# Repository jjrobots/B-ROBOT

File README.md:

JJROBOTS B-ROBOT
=================
Self Balancing Arduino robot. Control via Smartphone/Tablet. With Fully 3D printed parts.
New: This new version include support for the new V2 board! (with integrated ESP wifi module)

All the documentation, features, how it works, build manuals and SHOP here:
URL: http://jjrobots.com/b-robot

This is the new and well improved version of the old project:
Blog: http://cienciaycacharreo.blogspot.com.es/2013/10/b-robot-un-robot-equilibrista-impreso_28.html

To install code read the install.txt instructions

JJROBOTS 2015. Science & fun!

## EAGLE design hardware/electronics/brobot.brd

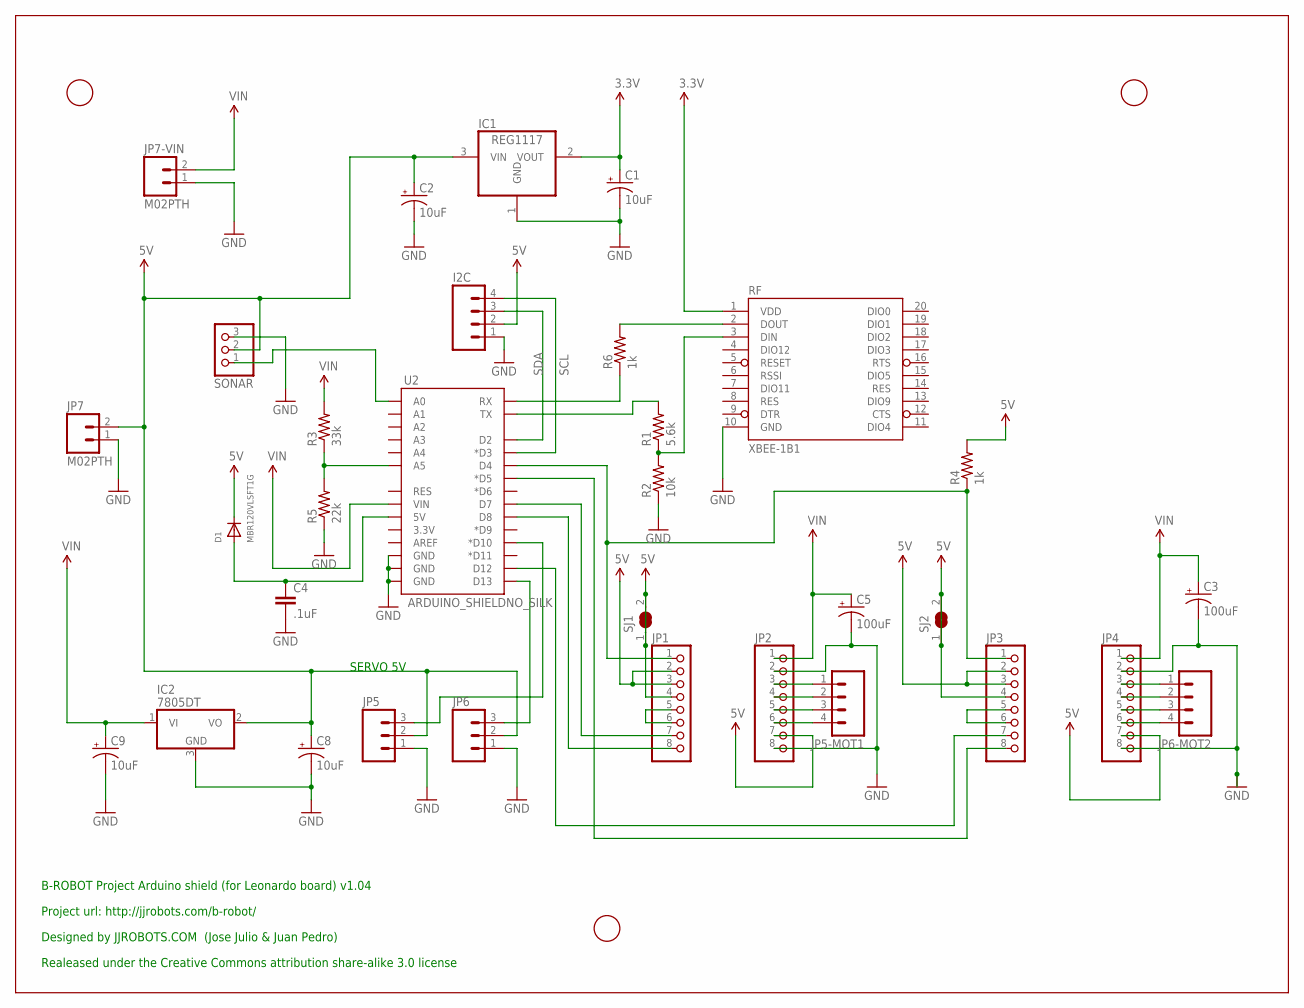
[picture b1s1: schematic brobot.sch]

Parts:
C1, C2, C8, C9: 10uF; EIA3216
C3, C5: 100uF; PANASONIC_D
C4: .1uF; 0402-CAP
D1: MBR120VLSFT1G; SOD-123
I2C: M04PTH; 1X04
IC1: REG1117; SOT223
IC2: 7805DT; TO252
JP1, JP2, JP3, JP4: PINHD-1X8; 1X08
JP5, JP6: M03PTH; 1X03
JP5-MOT1, JP6-MOT2: M04PTH; 1X04
JP7, JP7-VIN: M02PTH; 1X02
R1: 5.6k; 0805
R2: 10k; 0805
R3: 33k; 0805
R4, R6: 1k; 0805
R5: 22k; 0805
RF: XBEE-1B1; XBEE-1
SJ1, SJ2: SJW
SONAR: PINHD-1X3; 1X03
U2: ARDUINO_SHIELDNO_SILK; DUEMILANOVE_VIAS
U$1, U$2, U$3: FIDUCIAL; FIDUCIAL_1MM

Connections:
3.3V: C1.A (+), IC1.2 (VOUT), RF.1 (VDD)
5V: C2.A (+), C8.A (+), D1.C, I2C.2, IC1.3 (VIN), IC2.2 (VO), JP1.2, JP1.3, JP1.4, JP2.7, JP3.2, JP3.3, JP3.4, JP4.7, JP5.2, JP6.2, JP7.2, R4.2, SJ1.1, SJ1.2, SJ2.1, SJ2.2, SONAR.2
GND: C1.C (-), C2.C (-), C3.-, C4.2, C5.-, C8.C (-), C9.C (-), I2C.1, IC1.1 (GND), IC2.3 (GND), JP2.2, JP2.8, JP4.2, JP4.8, JP5.1, JP6.1, JP7.1, JP7-VIN.1, R2.1, R5.1, RF.10 (GND), SONAR.3, U2.GND@0 (GND), U2.GND@1 (GND), U2.GND@2 (GND)
unnamed: JP2.3, JP5-MOT1.1
unnamed: JP2.4, JP5-MOT1.2
unnamed: R6.2, RF.2 (DOUT)
unnamed: R1.1, R2.2, RF.3 (DIN)
unnamed: R1.2, U2.TX
unnamed: JP2.5, JP5-MOT1.3
unnamed: JP2.6, JP5-MOT1.4
unnamed: JP4.3, JP6-MOT2.1
unnamed: JP4.4, JP6-MOT2.2
unnamed: JP4.5, JP6-MOT2.3
unnamed: JP1.5, JP1.6
unnamed: JP3.5, JP3.6
unnamed: R3.1, R5.2, U2.A5
unnamed: R6.1, U2.RX
unnamed: SONAR.1, U2.A0
unnamed: JP4.6, JP6-MOT2.4
unnamed: JP6.3, U2.D13
unnamed: JP5.3, U2.D10 (*D10)
unnamed: JP1.8, U2.D8
unnamed: JP1.7, U2.D7
unnamed: JP1.1, JP3.1, R4.1, U2.D4
unnamed: JP3.8, U2.D5 (*D5)
unnamed: JP3.7, U2.D12
unnamed: C4.1, D1.A, U2.5V
SCL: I2C.4, U2.D3 (*D3)
SDA: I2C.3, U2.D2
VIN: C3.+, C5.+, C9.A (+), IC2.1 (VI), JP2.1, JP4.1, JP7-VIN.2, R3.2, U2.VIN

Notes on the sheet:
SERVO 5V
Project url: http://jjrobots.com/b-robot/
Designed by JJROBOTS.COM (Jose Julio & Juan Pedro)
Realeased under the Creative Commons attribution share-alike 3.0 license
B-ROBOT Project Arduino shield (for Leonardo board) v1.04

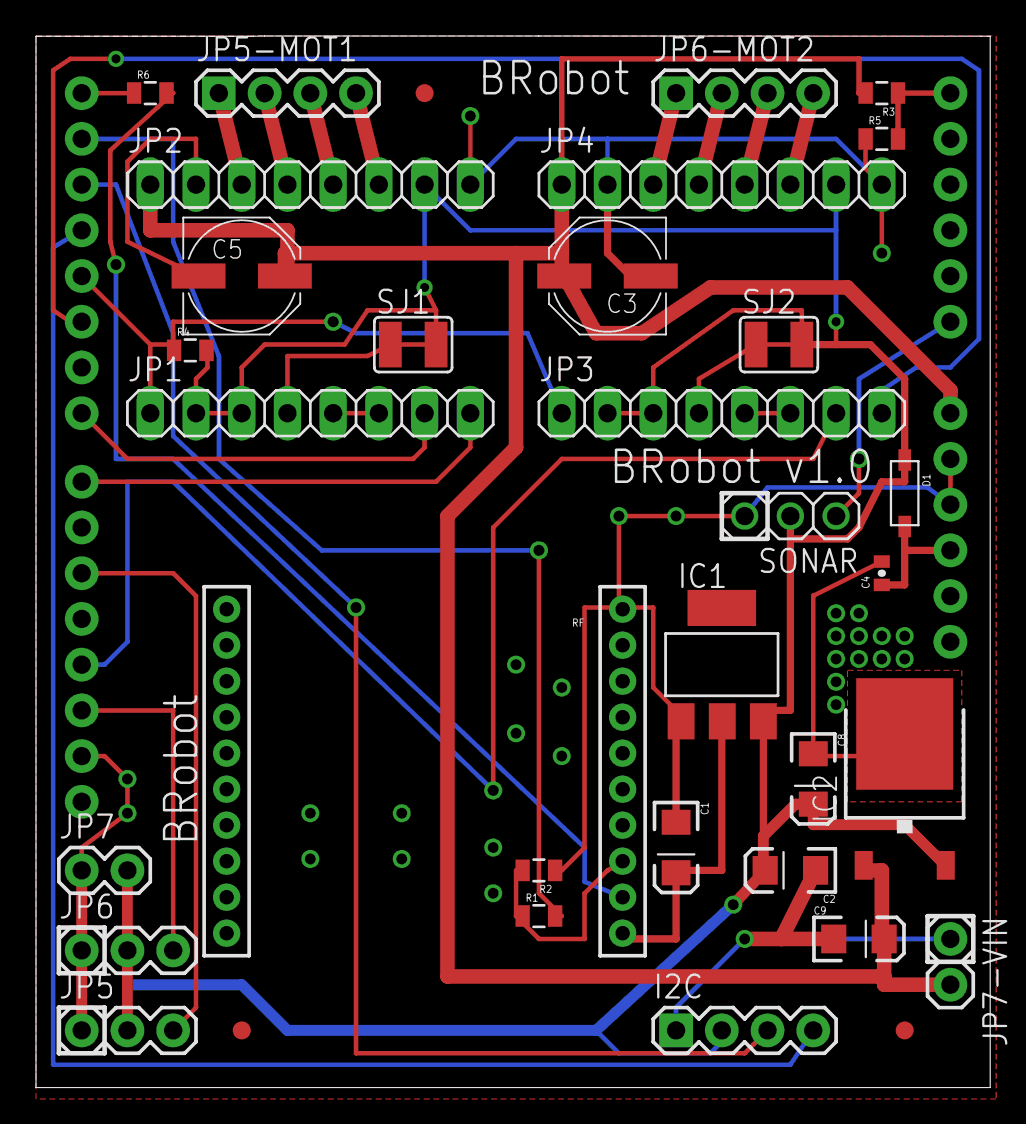
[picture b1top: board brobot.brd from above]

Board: 2 copper layers, 53.0 x 58.4 mm, 35 parts (0 on the bottom side), 30 nets.

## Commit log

2015-02-15 :octocat: Added .gitattributes & .gitignore files
2015-02-20 BROBOT code
    BROBOT code, libraries, 3DParts, interface...
2015-02-21 Readme update
2015-02-21 B-robot STL models
    3D parts models of the B-robot
2015-02-23 Wifi configuration utility
    Arduino sketch to configure Wifi module
2015-02-25 Electronic schem and board
    added electronic schem and board of B-ROBOT brain shield
2015-02-25 Schematic on PDF format
    Electronic schem on PDF format (easy for users)
2015-03-05 Compatibility with firmware 4.41
    Added compatibility for new 4.41 firmware. Added WPA2 security for Soft
    AP (new in 4.41)
2015-03-05 Added echo mode to test
    At the end of the configuration process, the code starts an echo mode to
    test the module
2015-03-05 Added bidirectional test mode
    Added bidirectional test mode. Now it´s posible to test and also check
    configure the module (command mode).
2015-08-19 Support for new V2 board
    This version support the new board (V2) with the ESP wifi module
    integrated.
2015-08-19 New v2 version support
    Comment of new V2 board support with integrated wifi module
2015-08-24 OSC library update
    OSC library update (needed for new V2 code)
2015-11-02 New library versions
    New library versions.
    JJROBOTS_BROBOT -> new servo2 support on Timer4
    JJROBOTS_OSC -> Updated MsgSend to send messages using OSC from Robot to
    Interface. Support for OSC TouchMessages (/z) on fader1 and fader2 to
    reset controls
2015-11-02 New version
    New version with default parameters for BROBOT EVO version.
    Support for touchMessages(/z)
    Battery status on Interface
2015-11-02 New interface
    New interface with support to read the robot´s battery status.
2015-11-02 New EVO version 3D parts
    New EVO version 3D parts

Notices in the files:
parts and their libraries:
SparkFun-Boards: Licensing: Creative Commons ShareAlike 4.0 International - https://creativecommons.org/licenses/by-sa/4.0
